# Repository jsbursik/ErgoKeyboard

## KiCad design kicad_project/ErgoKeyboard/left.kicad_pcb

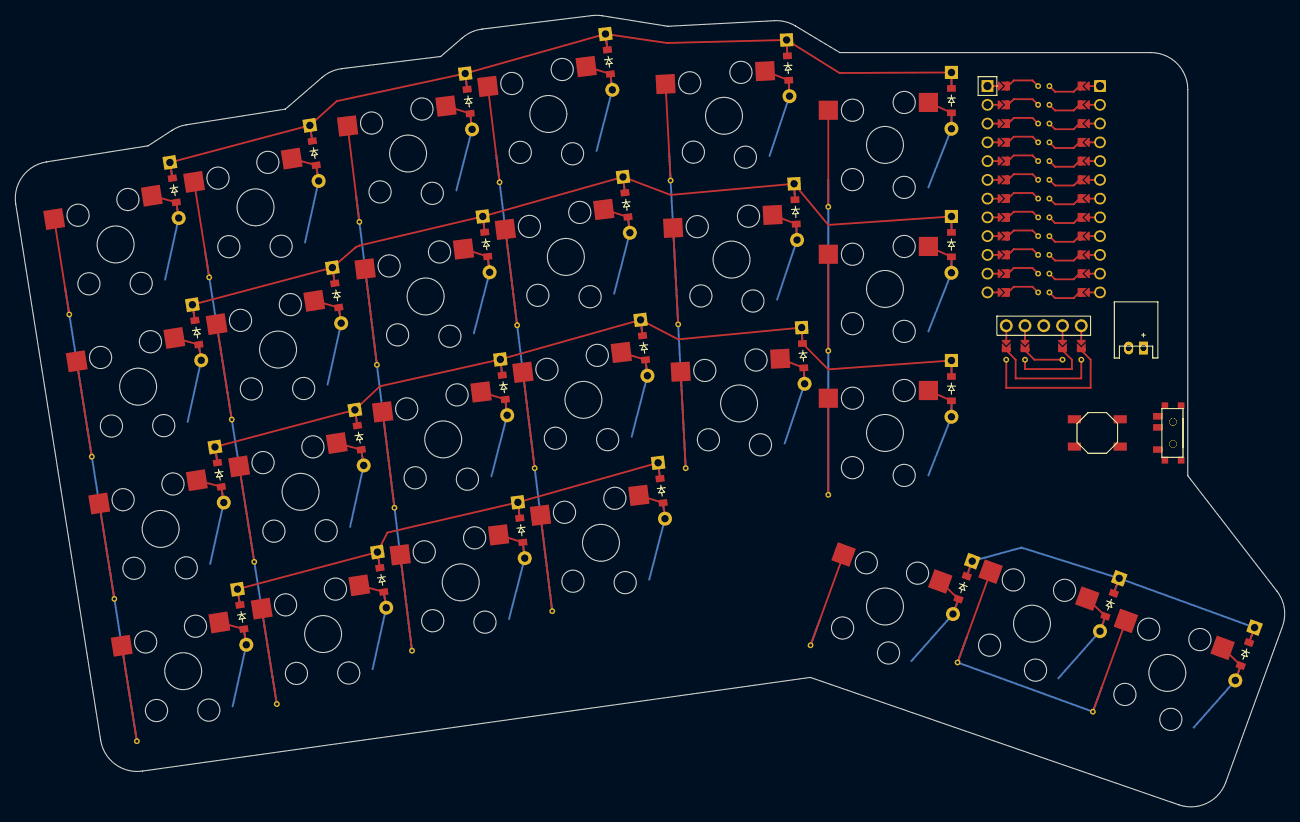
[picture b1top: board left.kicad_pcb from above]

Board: 2 copper layers, 171.9 x 107.2 mm, 58 parts (0 on the bottom side), 39 nets.

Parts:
B1, B2: SW_TACT_ALPS_SKQGABE010
D1, D2, D3, D4, D5, D6, D7, D8, D9, D10, D11, D12, D13, D14, D15, D16, D17, D18, D19, D20, D21, D22, D23, D24, D25: ComboDiode
JST1, JST2: JST_PH_S2B-PH-K_02x2.00mm_Angled
MCU1: ProMicro
OLED1: nice!view; niceview
S1, S2, S3, S4, S5, S6, S7, S8, S9, S10, S11, S12, S13, S14, S15, S16, S17, S18, S19, S20, S21, S22, S23, S24, S25: ks27; gateron-ks27
T1, T2: SPDT_C128955

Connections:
BPOS: JST1.1, JST2.1, T1.1, T2.1
GND: B1.1, B2.1, JST1.2, JST2.2, MCU1.2, MCU1.21, MCU1.22
P6: D4.1, D8.1, D12.1, D16.1, D19.1, D22.1, MCU1.16
P7: D3.1, D7.1, D11.1, D15.1, D18.1, D21.1, MCU1.15
P8: D2.1, D6.1, D10.1, D14.1, D17.1, D20.1, MCU1.14
P9: D1.1, D5.1, D9.1, D13.1, D23.1, D24.1, D25.1, MCU1.13
P10: MCU1.12, S1.1, S2.1, S3.1, S4.1
P14: MCU1.10, S9.1, S10.1, S11.1, S12.1
P15: MCU1.9, S13.1, S14.1, S15.1, S16.1
P16: MCU1.11, S5.1, S6.1, S7.1, S8.1
P18: MCU1.8, S17.1, S18.1, S19.1, S23.1
P19: MCU1.7, S20.1, S21.1, S22.1, S24.1, S25.1
RST: B1.2, B2.2, MCU1.3
VCC: MCU1.4, OLED1.3, T1.2, T2.2
home_cluster: D24.2, S24.2
index_bottom: D17.2, S17.2
index_home: D18.2, S18.2
index_top: D19.2, S19.2
inner_bottom: D20.2, S20.2
inner_cluster: D25.2, S25.2
inner_home: D21.2, S21.2
inner_top: D22.2, S22.2
middle_bottom: D14.2, S14.2
middle_home: D15.2, S15.2
middle_mod: D13.2, S13.2
middle_top: D16.2, S16.2
outer_bottom: D2.2, S2.2
outer_cluster: D23.2, S23.2
outer_home: D3.2, S3.2
outer_mod: D1.2, S1.2
outer_top: D4.2, S4.2
pinky_bottom: D6.2, S6.2
pinky_home: D7.2, S7.2
pinky_mod: D5.2, S5.2
pinky_top: D8.2, S8.2
ring_bottom: D10.2, S10.2
ring_home: D11.2, S11.2
ring_mod: D9.2, S9.2
ring_top: D12.2, S12.2

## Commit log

2023-08-24 work on footprints, possible new start
2023-08-25 Updated to add build script
2023-08-25 Rewrote design, started pcb work
2023-08-25 fixed minor mistake with params
2023-08-25 rewrote for up orientation, fixed typo
2023-08-25 generated stuff, req's cleanup
2023-08-25 fixes for reversible fp
2023-08-25 fix to pinout
2023-08-25 translated and working (I think)
2023-08-25 added some components, tuning
2023-08-29 trying to add reversible pm fp
2023-09-28 staging programmatic footprint
2023-09-29 debugging footprint code
2023-10-01 completed reversible micro fp, working on layout
2023-10-02 positioned jsth, need jumper fp for revers. oled
2023-10-02 fixed most reversible stuff added footprints
2023-10-03 starting the netting process
2023-11-21 DRC doesn't like the smd trace hack, ouch
2023-11-24 using promicro pretty now, reverted some changes
2023-11-28 niceview reworked to "pretty" method
2023-11-29 fixed oled, started routing
2023-11-29 trying some stuff out
